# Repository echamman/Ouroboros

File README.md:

Ouroboros is a fuzzy delay and reverb based on the Daisy Seed

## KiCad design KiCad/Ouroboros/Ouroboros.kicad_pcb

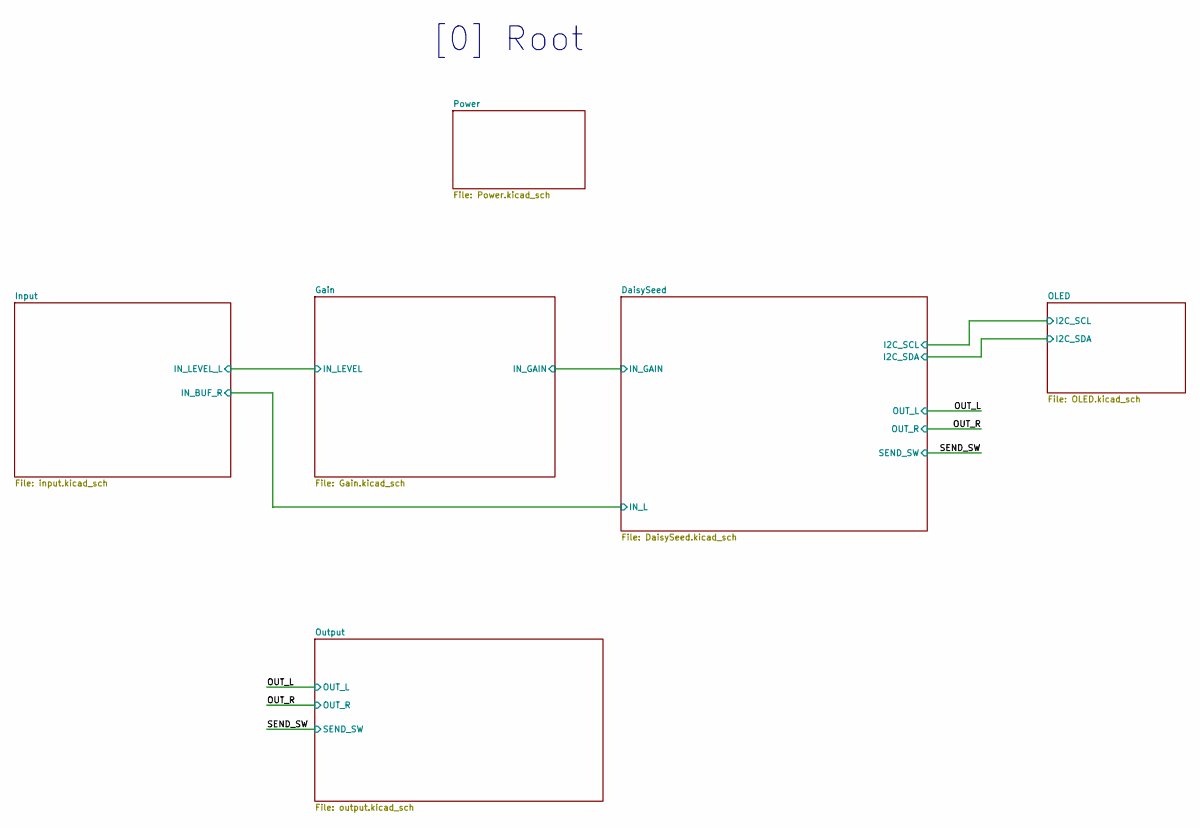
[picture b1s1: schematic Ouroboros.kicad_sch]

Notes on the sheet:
[0] Root

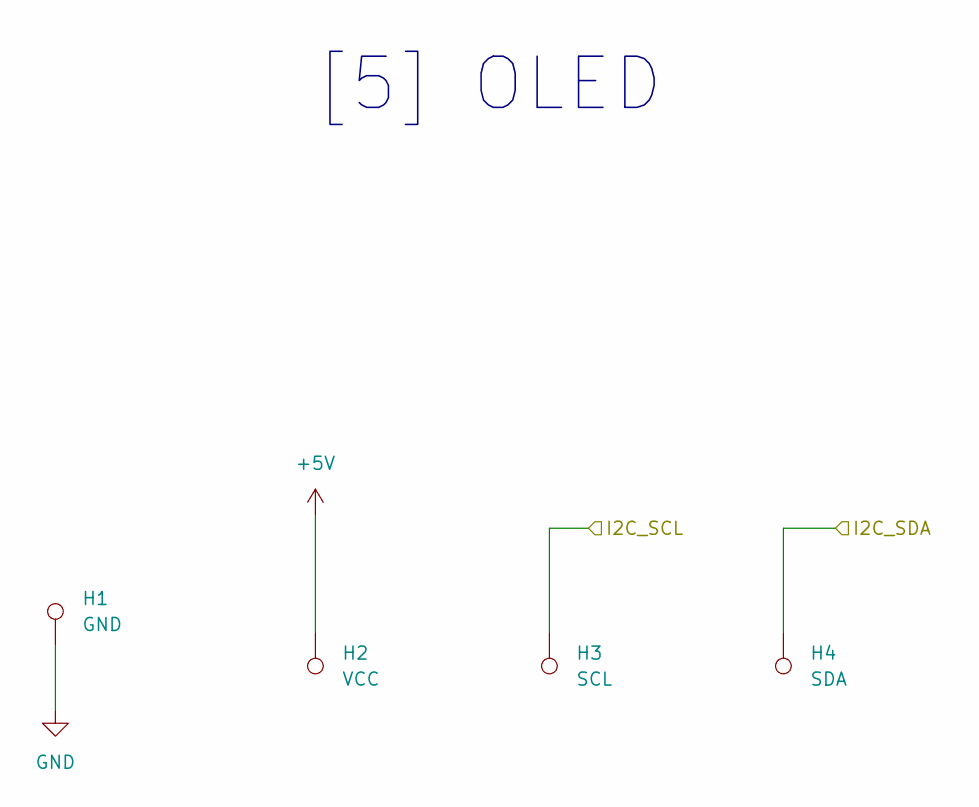
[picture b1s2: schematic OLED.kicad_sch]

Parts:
H1: GND; TestPoint_THTPad_D1.5mm_Drill0.7mm
H2: VCC; TestPoint_THTPad_D1.5mm_Drill0.7mm
H3: SCL; TestPoint_THTPad_D1.5mm_Drill0.7mm
H4: SDA; TestPoint_THTPad_D1.5mm_Drill0.7mm

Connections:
+5V: H2.1; also elsewhere on the board
/DaisySeed/I2C_SCL: H3.1; also elsewhere on the board
/DaisySeed/I2C_SDA: H4.1; also elsewhere on the board
GND: H1.1; also elsewhere on the board

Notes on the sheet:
[5] OLED

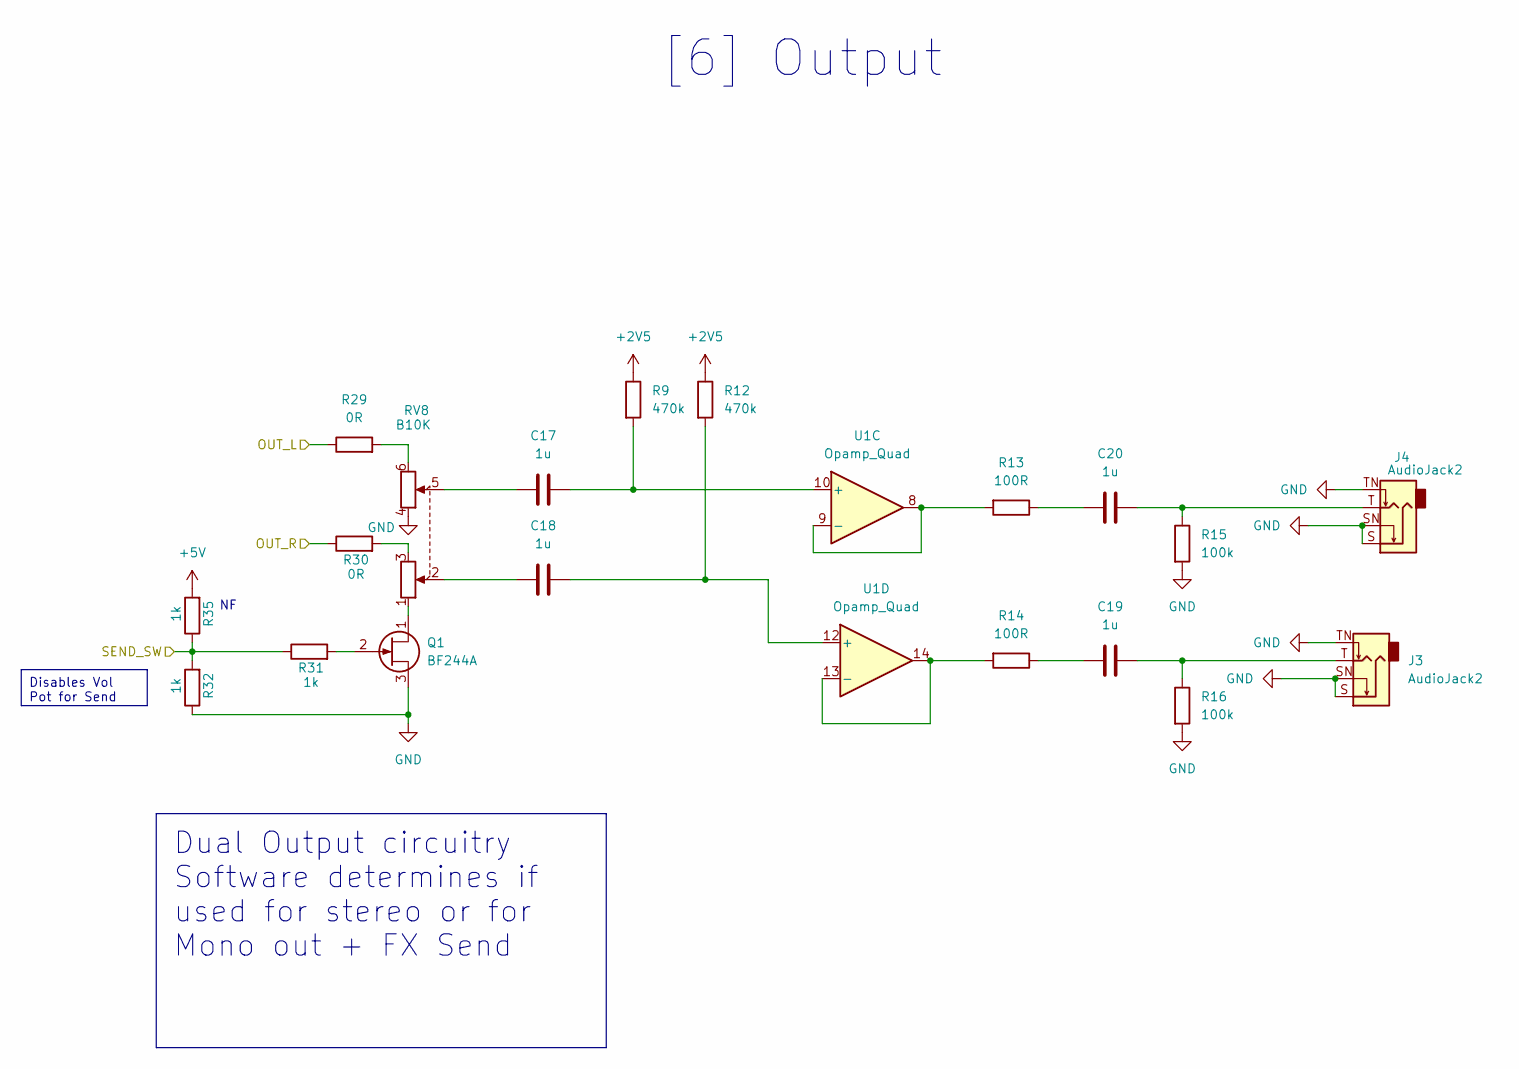
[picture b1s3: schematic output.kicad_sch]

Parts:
C17, C18, C19, C20: 1u; C_Rect_L7.0mm_W6.0mm_P5.00mm
J3, J4: AudioJack2; Jack_6.35mm_Neutrik_NMJ4HFD2_Horizontal
Q1: BF244A; TO-92_Inline
R9, R12: 470k; R_Axial_DIN0207_L6.3mm_D2.5mm_P10.16mm_Horizontal
R13, R14: 100R; R_Axial_DIN0207_L6.3mm_D2.5mm_P10.16mm_Horizontal
R15, R16: 100k; R_Axial_DIN0207_L6.3mm_D2.5mm_P10.16mm_Horizontal
R29, R30: 0R; R_Axial_DIN0204_L3.6mm_D1.6mm_P1.90mm_Vertical
R31, R32, R35: 1k; R_Axial_DIN0207_L6.3mm_D2.5mm_P10.16mm_Horizontal
RV8: B10K; Potentiometer_Alpha_RD902F-40-00D_Dual_Vertical
U1: Opamp_Quad; DIP-14_W7.62mm_Socket

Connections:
+2V5: R9.1, R12.1; also elsewhere on the board
+5V: R35.2; also elsewhere on the board
/OUT_L: R29.1; also elsewhere on the board
/OUT_R: R30.1; also elsewhere on the board
/SEND_SW: R31.1, R32.2, R35.1; also elsewhere on the board
GND: J3.S, J3.SN, J3.TN, J4.S, J4.SN, J4.TN, Q1.3 (S), R15.2, R16.2, R32.1, RV8.4; also elsewhere on the board
unnamed: C17.1, RV8.5
unnamed: C18.1, RV8.2
unnamed: C19.1, R14.1
unnamed: C19.2, J3.T, R16.1
unnamed: C20.1, R13.1
unnamed: C20.2, J4.T, R15.1
unnamed: Q1.1 (D), RV8.1
unnamed: Q1.2 (G), R31.2
unnamed: R29.2, RV8.6
unnamed: R30.2, RV8.3
unnamed: C17.2, R9.2, U1.10 (+)
unnamed: R13.2, U1.8, U1.9 (-)
unnamed: C18.2, R12.2, U1.12 (+)
unnamed: R14.2, U1.13 (-), U1.14

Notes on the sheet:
Disables Vol Pot for Send
Dual Output circuitry Software determines if used for stereo or for Mono out + FX Send
[6] Output

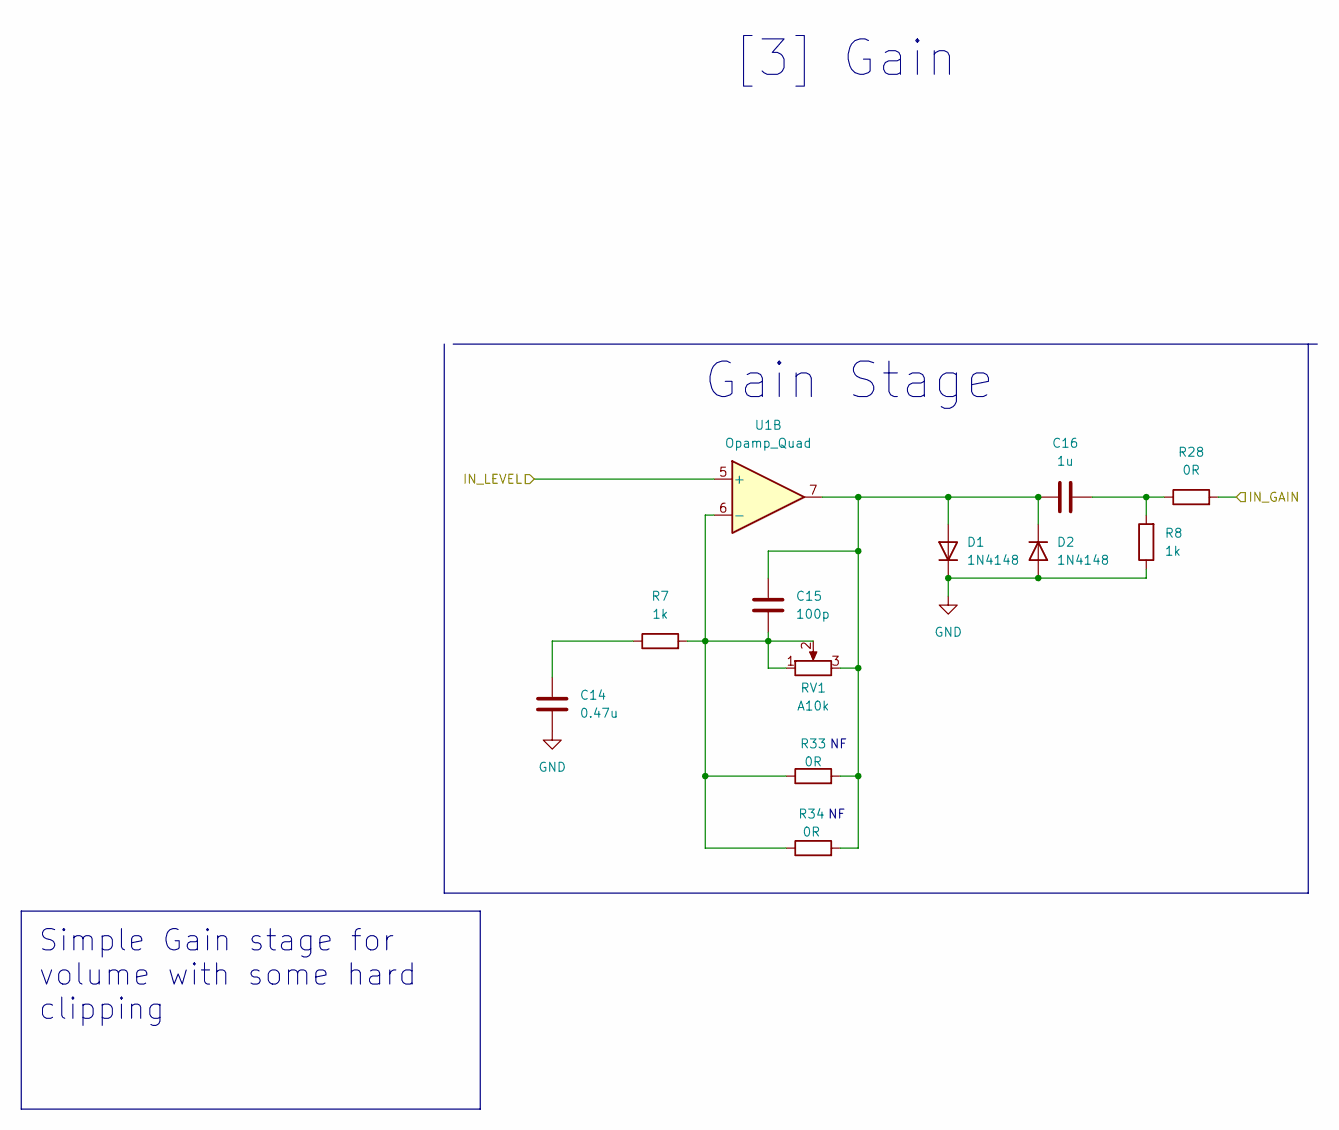
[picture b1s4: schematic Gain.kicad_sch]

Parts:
C14: 0.47u; C_Rect_L7.0mm_W3.5mm_P5.00mm
C15: 100p; C_Rect_L7.0mm_W3.5mm_P5.00mm
C16: 1u; C_Rect_L7.0mm_W6.0mm_P5.00mm
D1, D2: 1N4148; D_DO-35_SOD27_P7.62mm_Horizontal
R7, R8: 1k; R_Axial_DIN0207_L6.3mm_D2.5mm_P10.16mm_Horizontal
R28: 0R; R_Axial_DIN0204_L3.6mm_D1.6mm_P1.90mm_Vertical
R33, R34: 0R; R_Axial_DIN0207_L6.3mm_D2.5mm_P10.16mm_Horizontal
RV1: A10k; Potentiometer_Alpha_RD901F-40-00D_Single_Vertical
U1: Opamp_Quad; DIP-14_W7.62mm_Socket

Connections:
/DaisySeed/IN_GAIN: R28.2; also elsewhere on the board
/Gain/IN_LEVEL: U1.5 (+); also elsewhere on the board
GND: C14.2, D1.1 (K), D2.2 (A), R8.1; also elsewhere on the board
unnamed: C14.1, R7.1
unnamed: C16.2, R8.2, R28.1
unnamed: C15.1, C16.1, D1.2 (A), D2.1 (K), R33.2, R34.2, RV1.3, U1.7
unnamed: C15.2, R7.2, R33.1, R34.1, RV1.1, RV1.2, U1.6 (-)

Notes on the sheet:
Simple Gain stage for volume with some hard clipping
Gain Stage
[3] Gain

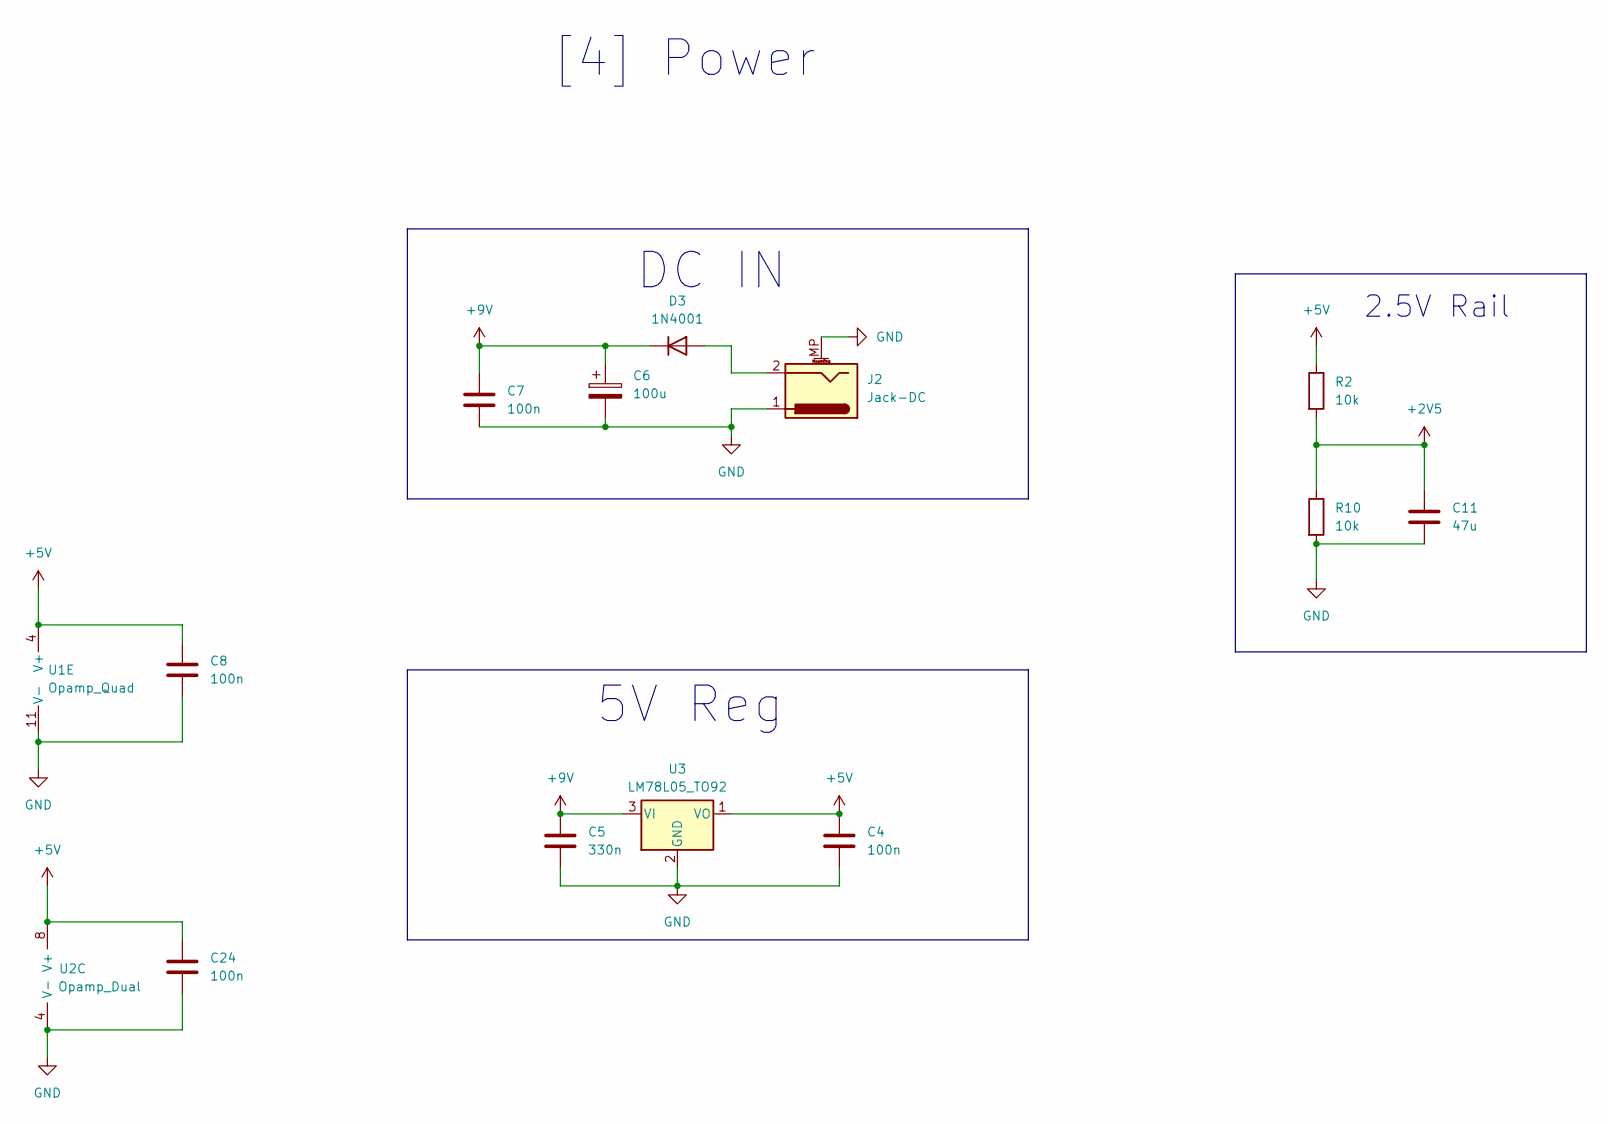
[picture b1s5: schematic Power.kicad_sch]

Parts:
C4, C7, C8, C24: 100n; C_Rect_L7.0mm_W3.5mm_P5.00mm
C5: 330n; C_Rect_L7.0mm_W3.5mm_P5.00mm
C6: 100u; CP_Radial_D5.0mm_P2.50mm
C11: 47u; C_Rect_L7.0mm_W3.5mm_P5.00mm
D3: 1N4001; D_DO-41_SOD81_P10.16mm_Horizontal
J2: Jack-DC; BarrelJack_CUI_PJ-063AH_Horizontal_CircularHoles
R2, R10: 10k; R_Axial_DIN0207_L6.3mm_D2.5mm_P10.16mm_Horizontal
U1: Opamp_Quad; DIP-14_W7.62mm_Socket
U2: Opamp_Dual; DIP-8_W7.62mm_Socket
U3: LM78L05_TO92; TO-92_Inline

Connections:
+2V5: C11.1, R2.2, R10.1; also elsewhere on the board
+5V: C4.1, C8.1, C24.1, R2.1, U1.4 (V+), U2.8 (V+), U3.1 (VO); also elsewhere on the board
+9V: C5.1, C6.1, C7.1, D3.1 (K), U3.3 (VI); also elsewhere on the board
GND: C4.2, C5.2, C6.2, C7.2, C8.2, C11.2, C24.2, J2.1, J2.MP (MountPin), R10.2, U1.11 (V-), U2.4 (V-), U3.2 (GND); also elsewhere on the board
unnamed: D3.2 (A), J2.2

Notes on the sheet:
DC IN
[4] Power
5V Reg
2.5V Rail

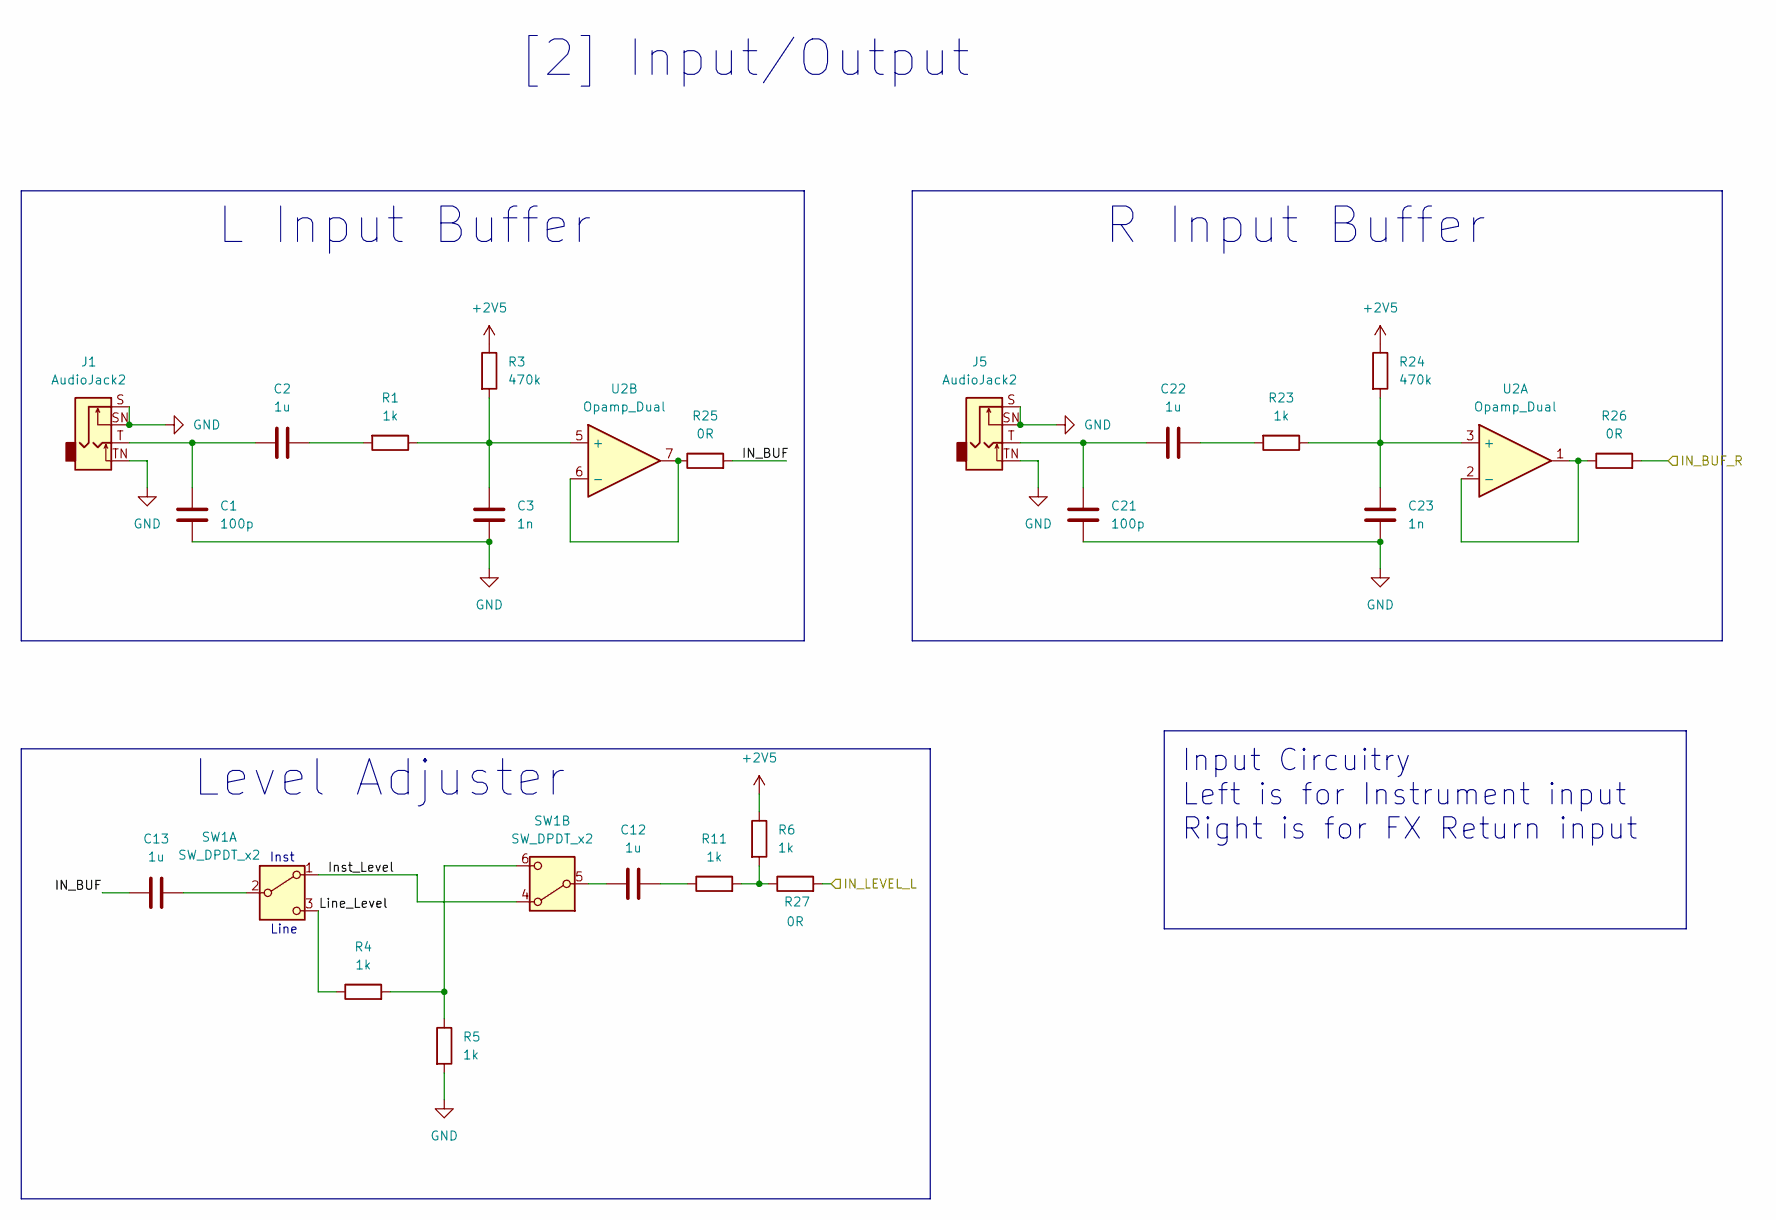
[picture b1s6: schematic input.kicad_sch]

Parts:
C1, C21: 100p; C_Rect_L7.0mm_W3.5mm_P5.00mm
C2, C22: 1u; C_Rect_L7.0mm_W6.0mm_P5.00mm
C3, C23: 1n; C_Rect_L7.0mm_W3.5mm_P5.00mm
C12, C13: 1u; C_Rect_L7.0mm_W3.5mm_P5.00mm
J1, J5: AudioJack2; Jack_6.35mm_Neutrik_NMJ4HFD2_Horizontal
R1, R4, R5, R6, R11, R23: 1k; R_Axial_DIN0207_L6.3mm_D2.5mm_P10.16mm_Horizontal
R3, R24: 470k; R_Axial_DIN0207_L6.3mm_D2.5mm_P10.16mm_Horizontal
R25, R26, R27: 0R; R_Axial_DIN0204_L3.6mm_D1.6mm_P1.90mm_Vertical
SW1: SW_DPDT_x2; DPDT_Mini_Toggle
U2: Opamp_Dual; DIP-8_W7.62mm_Socket

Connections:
+2V5: R3.1, R6.1, R24.1; also elsewhere on the board
/DaisySeed/IN_L: R26.2; also elsewhere on the board
/Gain/IN_LEVEL: R27.2; also elsewhere on the board
/Input/IN_BUF: C13.1, R25.2
/Input/Inst_Level: SW1.1 (A), SW1.4 (A)
/Input/Line_Level: R4.1, SW1.3 (C)
GND: C1.2, C3.2, C21.2, C23.2, J1.S, J1.SN, J1.TN, J5.S, J5.SN, J5.TN, R5.2; also elsewhere on the board
unnamed: C1.1, C2.1, J1.T
unnamed: C2.2, R1.2
unnamed: C12.2, R11.1
unnamed: C21.1, C22.1, J5.T
unnamed: C22.2, R23.2
unnamed: R6.2, R11.2, R27.1
unnamed: C13.2, SW1.2 (B)
unnamed: C12.1, SW1.5 (B)
unnamed: R4.2, R5.1, SW1.6 (C)
unnamed: C23.1, R23.1, R24.2, U2.3 (+)
unnamed: R26.1, U2.1, U2.2 (-)
unnamed: C3.1, R1.1, R3.2, U2.5 (+)
unnamed: R25.1, U2.6 (-), U2.7

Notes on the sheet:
Input Circuitry Left is for Instrument input Right is for FX Return input
L Input Buffer
Level Adjuster
R Input Buffer
Inst
Line
[2] Input/Output

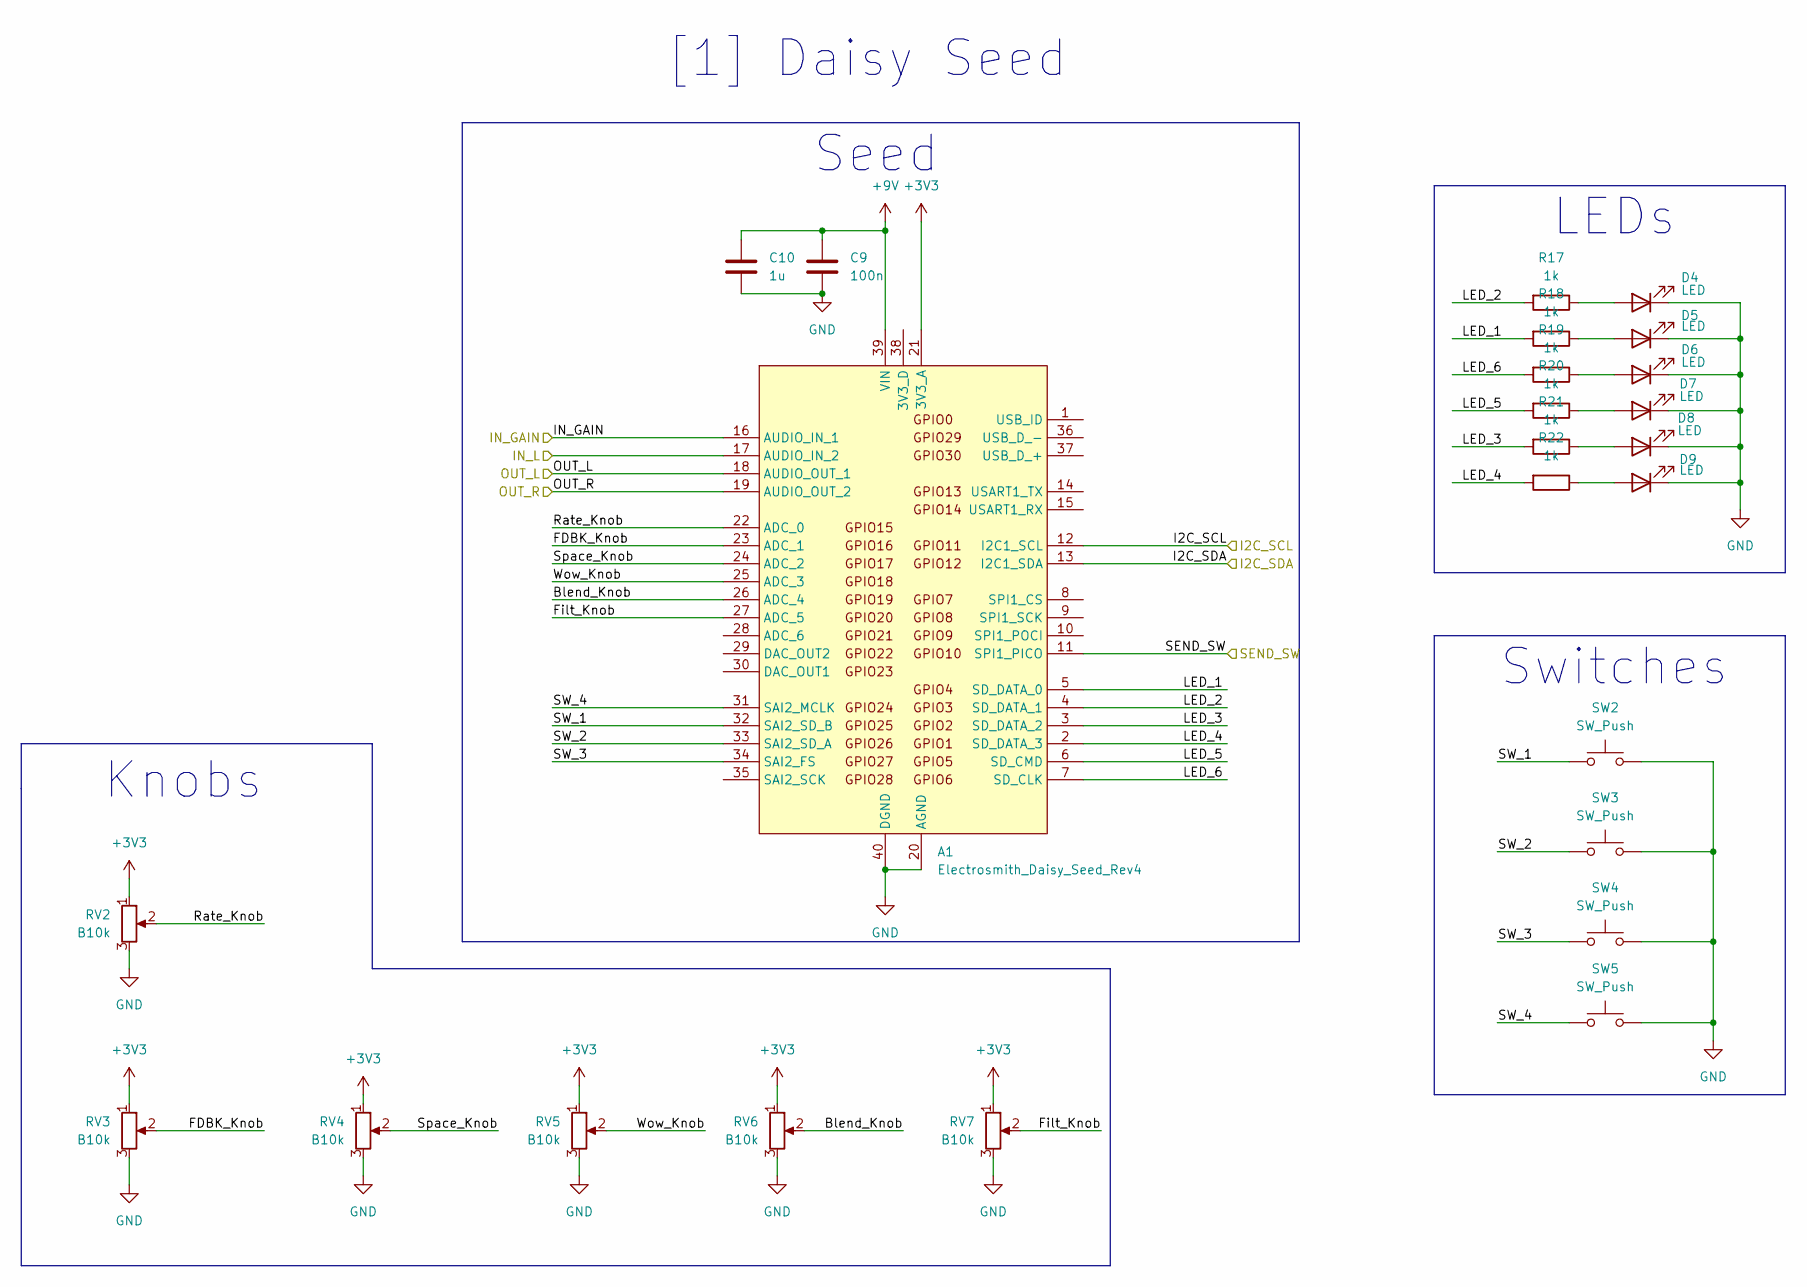
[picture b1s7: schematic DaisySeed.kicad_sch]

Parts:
A1: Electrosmith_Daisy_Seed_Rev4; Electrosmith_Daisy_Seed
C9: 100n; C_Rect_L7.0mm_W3.5mm_P5.00mm
C10: 1u; C_Rect_L7.0mm_W6.0mm_P5.00mm
D4, D5, D6, D7, D8, D9: LED; LED_D3.0mm
R17, R18, R19, R20, R21, R22: 1k; R_Axial_DIN0207_L6.3mm_D2.5mm_P10.16mm_Horizontal
RV2, RV3, RV4, RV5, RV6, RV7: B10k; Potentiometer_Alpha_RD901F-40-00D_Single_Vertical
SW2, SW3, SW4, SW5: SW_Push; SW_Cherry_MX_1.00u_PCB

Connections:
+3V3: A1.21 (3V3_A), RV2.1, RV3.1, RV4.1, RV5.1, RV6.1, RV7.1
+9V: A1.39 (VIN), C9.1, C10.1; also elsewhere on the board
/DaisySeed/Blend_Knob: A1.26 (ADC_4), RV6.2
/DaisySeed/FDBK_Knob: A1.23 (ADC_1), RV3.2
/DaisySeed/Filt_Knob: A1.27 (ADC_5), RV7.2
/DaisySeed/I2C_SCL: A1.12 (I2C1_SCL); also elsewhere on the board
/DaisySeed/I2C_SDA: A1.13 (I2C1_SDA); also elsewhere on the board
/DaisySeed/IN_GAIN: A1.16 (AUDIO_IN_1); also elsewhere on the board
/DaisySeed/IN_L: A1.17 (AUDIO_IN_2); also elsewhere on the board
/DaisySeed/LED_1: A1.5 (SD_DATA_0), R18.2
/DaisySeed/LED_2: A1.4 (SD_DATA_1), R17.2
/DaisySeed/LED_3: A1.3 (SD_DATA_2), R21.2
/DaisySeed/LED_4: A1.2 (SD_DATA_3), R22.2
/DaisySeed/LED_5: A1.6 (SD_CMD), R20.2
/DaisySeed/LED_6: A1.7 (SD_CLK), R19.2
/DaisySeed/Rate_Knob: A1.22 (ADC_0), RV2.2
/DaisySeed/SW_1: A1.32 (SAI2_SD_B), SW2.1
/DaisySeed/SW_2: A1.33 (SAI2_SD_A), SW3.1
/DaisySeed/SW_3: A1.34 (SAI2_FS), SW4.1
/DaisySeed/SW_4: A1.31 (SAI2_MCLK), SW5.1
/DaisySeed/Space_Knob: A1.24 (ADC_2), RV4.2
/DaisySeed/Wow_Knob: A1.25 (ADC_3), RV5.2
/OUT_L: A1.18 (AUDIO_OUT_1); also elsewhere on the board
/OUT_R: A1.19 (AUDIO_OUT_2); also elsewhere on the board
/SEND_SW: A1.11 (SPI1_PICO); also elsewhere on the board
GND: A1.20 (AGND), A1.40 (DGND), C9.2, C10.2, D4.1 (K), D5.1 (K), D6.1 (K), D7.1 (K), D8.1 (K), D9.1 (K), RV2.3, RV3.3, RV4.3, RV5.3, RV6.3, RV7.3, SW2.2, SW3.2, SW4.2, SW5.2; also elsewhere on the board
unnamed: D4.2 (A), R17.1
unnamed: D5.2 (A), R18.1
unnamed: D6.2 (A), R19.1
unnamed: D7.2 (A), R20.1
unnamed: D8.2 (A), R21.1
unnamed: D9.2 (A), R22.1

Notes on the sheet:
Seed
[1] Daisy Seed
Switches
Knobs
LEDs

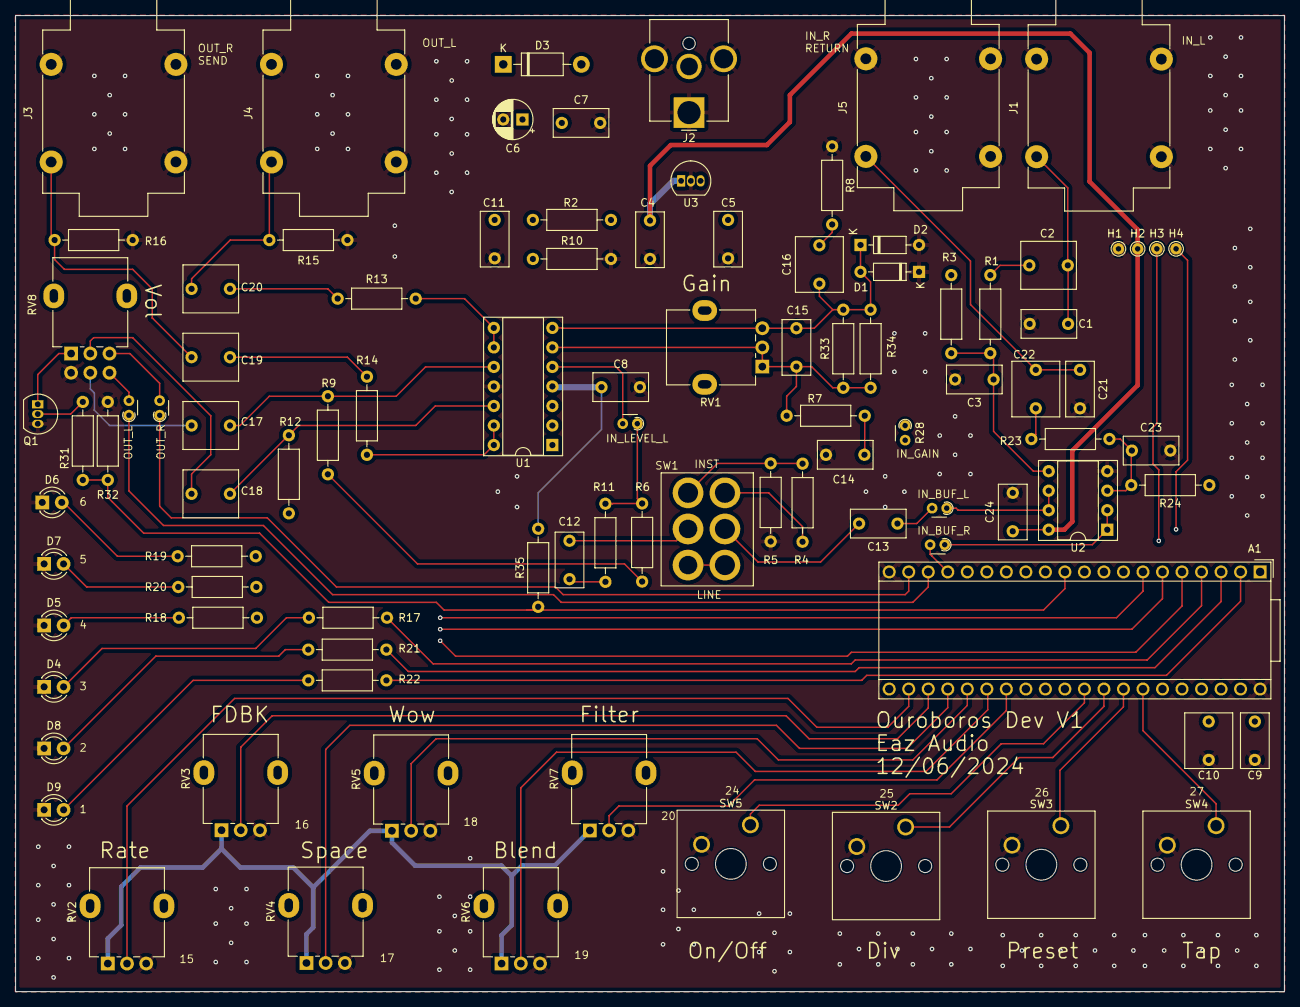
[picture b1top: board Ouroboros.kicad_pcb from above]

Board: 4 copper layers, 165.1 x 127.0 mm, 95 parts (0 on the bottom side), 70 nets.

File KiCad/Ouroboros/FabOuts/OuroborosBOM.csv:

Reference,Value,Datasheet,Footprint,Qty,Tayda Cart,Tayda SKU
A1,Electrosmith_Daisy_Seed_Rev4,https://static1.squarespace.com/static/58d03fdc1b10e3bf44256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,Module:Electrosmith_Daisy_Seed,1,0,
"C1,C15,C21",100p,~,Capacitor_THT:C_Rect_L7.0mm_W3.5mm_P5.00mm,3,10,A-531
"C2,C10,C12,C13,C16,C17,C18,C19,C20,C22",1u,~,-- mixed values --,10,20,
"C3,C23",1n,~,Capacitor_THT:C_Rect_L7.0mm_W3.5mm_P5.00mm,2,,
"C4,C7,C8,C9,C24",100n,~,Capacitor_THT:C_Rect_L7.0mm_W3.5mm_P5.00mm,5,50,
C5,330n,~,Capacitor_THT:C_Rect_L7.0mm_W3.5mm_P5.00mm,1,,
C6,100u,~,Capacitor_THT:CP_Radial_D5.0mm_P2.50mm,1,,
C11,47u,~,Capacitor_THT:C_Rect_L7.0mm_W3.5mm_P5.00mm,1,,
C14,0.47u,~,Capacitor_THT:C_Rect_L7.0mm_W3.5mm_P5.00mm,1,,
"D1,D2",1N4148,https://assets.nexperia.com/documents/data-sheet/1N4148_1N4448.pdf,Diode_THT:D_DO-35_SOD27_P7.62mm_Horizontal,2,,
D3,1N4001,http://www.vishay.com/docs/88503/1n4001.pdf,Diode_THT:D_DO-41_SOD81_P10.16mm_Horizontal,1,,
"D4,D5,D6,D7,D8,D9",LED,~,LED_THT:LED_D3.0mm,6,,
H1,GND,~,TestPoint:TestPoint_THTPad_D1.5mm_Drill0.7mm,1,,
H2,VCC,~,TestPoint:TestPoint_THTPad_D1.5mm_Drill0.7mm,1,,
H3,SCL,~,TestPoint:TestPoint_THTPad_D1.5mm_Drill0.7mm,1,,
H4,SDA,~,TestPoint:TestPoint_THTPad_D1.5mm_Drill0.7mm,1,,
"J1,J3,J4,J5",AudioJack2,https://www.neutrik.com/en/product/nmj4hfd2,Connector_Audio:Jack_6.35mm_Neutrik_NMJ4HFD2_Horizontal,4,8,A-6041
J2,Jack-DC,~,Connector_BarrelJack:BarrelJack_CUI_PJ-063AH_Horizontal_CircularHoles,1,,
Q1,BF244A,https://media.digikey.com/pdf/Data%20Sheets/Fairchild%20PDFs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,Package_TO_SOT_THT:TO-92_Inline,1,,
"R1,R4,R5,R6,R7,R8,R11,R17,R18,R19,R20,R21,R22,R23,R31,R32,R35",1k,~,Resistor_THT:R_Axial_DIN0207_L6.3mm_D2.5mm_P10.16mm_Horizontal,17,,
"R2,R10",10k,~,Resistor_THT:R_Axial_DIN0207_L6.3mm_D2.5mm_P10.16mm_Horizontal,2,,
"R3,R9,R12,R24",470k,~,Resistor_THT:R_Axial_DIN0207_L6.3mm_D2.5mm_P10.16mm_Horizontal,4,,
"R13,R14",100R,~,Resistor_THT:R_Axial_DIN0207_L6.3mm_D2.5mm_P10.16mm_Horizontal,2,,
"R15,R16",100k,~,Resistor_THT:R_Axial_DIN0207_L6.3mm_D2.5mm_P10.16mm_Horizontal,2,,
"R25,R26,R27,R28,R29,R30,R33,R34",0R,~,-- mixed values --,8,,
RV1,A10k,~,Potentiometer_THT:Potentiometer_Alpha_RD901F-40-00D_Single_Vertical,1,3, A-1856
"RV2,RV3,RV4,RV5,RV6,RV7",B10k,~,Potentiometer_THT:Potentiometer_Alpha_RD901F-40-00D_Single_Vertical,6,12,A-1847
RV8,B10K,~,Potentiometer_THT:Potentiometer_Alpha_RD902F-40-00D_Dual_Vertical,1,3,A-6433
SW1,SW_DPDT_x2,~,Library:DPDT_Mini_Toggle,1,2,A-4568
"SW2,SW3,SW4,SW5",SW_Push,~,Button_Switch_Keyboard:SW_Cherry_MX_1.00u_PCB,4,,
U1,Opamp_Quad,http://www.ti.com/lit/ds/symlink/tl071.pdf,Package_DIP:DIP-14_W7.62mm_Socket,1,,
U2,Opamp_Dual,~,Package_DIP:DIP-8_W7.62mm_Socket,1,,
U3,LM78L05_TO92,https://www.onsemi.com/pub/Collateral/MC78L06A-D.pdf,Package_TO_SOT_THT:TO-92_Inline,1,,

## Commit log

2024-10-27 Setting up a basic delay
2024-10-28 Cleaning up
2024-11-01 Cleanup
2024-11-01 Adding OLED screen
2024-11-01 Removing build folder
2024-11-01 Removing more unused files
2024-11-03 Playing with Reverb
2024-11-03 Optimizing knob readings to fix scratchiness
2024-11-05 Refactoring
2024-11-08 Presets
2024-11-08 Flutter/wow improvements
2024-11-09 Tempo manager added, struggling with tap
2024-11-09 Fixing metro and LED flash
2024-11-09 adds shrek movie as a 7mb gif
2024-11-11 Tap tempo working
2024-11-15 Adding KiCad
2024-11-15 Updating schematic
2024-11-15 Linking nets
2024-12-01 Updated schematic, started PCB
2024-12-07 PCB Finished
2025-01-14 Dev Board complete
2025-01-22 Devboard V0.1 hardware mapping
2025-01-22 Devboard V0.2 Signal Path Overhaul
2025-01-22 Devboard V0.21 Initial SendReturn mode added
2025-01-23 Devboard V0.22 Added LP Filter
2025-01-23 Devboard V.23 Upgrade to LP + HP Filter
2025-01-23 Devboard V0.3 All modes added
2025-01-24 Devboard V0.31 button logic updated
2025-01-24 Devboard V0.32 Knob management cleaned up
2025-01-24 Devboard V0.33 optimizing code to only run value updates when knob or button moved
2025-01-25 Devboard V0.34 fixed crackling when changing rate
2025-02-01 Devboard V0.35 Updated presets to long/med/short
2025-02-01 Disabling flutter/wow
2025-02-04 Temporary fix for delaytime preset management
2025-02-04 Documents
